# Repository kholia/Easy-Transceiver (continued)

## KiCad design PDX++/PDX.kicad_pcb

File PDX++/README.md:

#### PDX++

A port of https://github.com/WB2CBA/ADX/ to Raspberry Pi Pico.

Bands covered: 80-meter to 10-meter.

The live FT8 audio can also be decoded on PC / RPi / Android phone.

Note: The PCB part is WIP (work-in-progress) at the moment.

####  Features

- Easy inbuilt and self-sufficient Si5351 calibration

- Native FT8 decoding on the Pico (via AA1GD)

- Native spotting (reporting to PSKReporter.info)

- Inbuilt BCI (broadcast interference) filter

#### BOM Sources

International users can buy from Mouser and DigiKey.

Here are some local BOM sources I use:

- https://inkocean.in/ - CD2003 (Chinese clone which is known to work fine)

- https://www.electronicscomp.com/ (SMD resistors + SMD caps + THT inductors)

  - All SMD caps and resistors are 1206 sized

- https://www.ktron.in/ (SMA connectors)

- https://www.comkey.in/ - Branded SMD stuff

- https://rarecomponents.com/store/1002 - NXP 1N4148

- https://projectpoint.in/ - CDIL 7805, PJ307 Stereo Socket

- https://www.evelta.com/l7805-positive-voltage-regulator-1-5a-5v/ (alternate)

- https://robu.in/product/si5351a-i2c-8-khz-160-mhz-clock-generator-breakout-board-module/

- https://robu.in/product/raspberry-pi-pico/

- https://etstore.in/ - OEN MICRO RELAY 46-05-2C

#### Credits

- https://github.com/WB2CBA/ADX/

- https://www.qrz.com/DB/VU2BGS

- https://github.com/aa1gd/pico_ft8_xcvr (AA1GD)

- https://github.com/lu7did/ADX

#### References

- https://github.com/kholia/pico_ft8_xcvr (firmware)

- https://f5npv.wordpress.com/homebrew-ft8qrp-afp-fsk-trx/

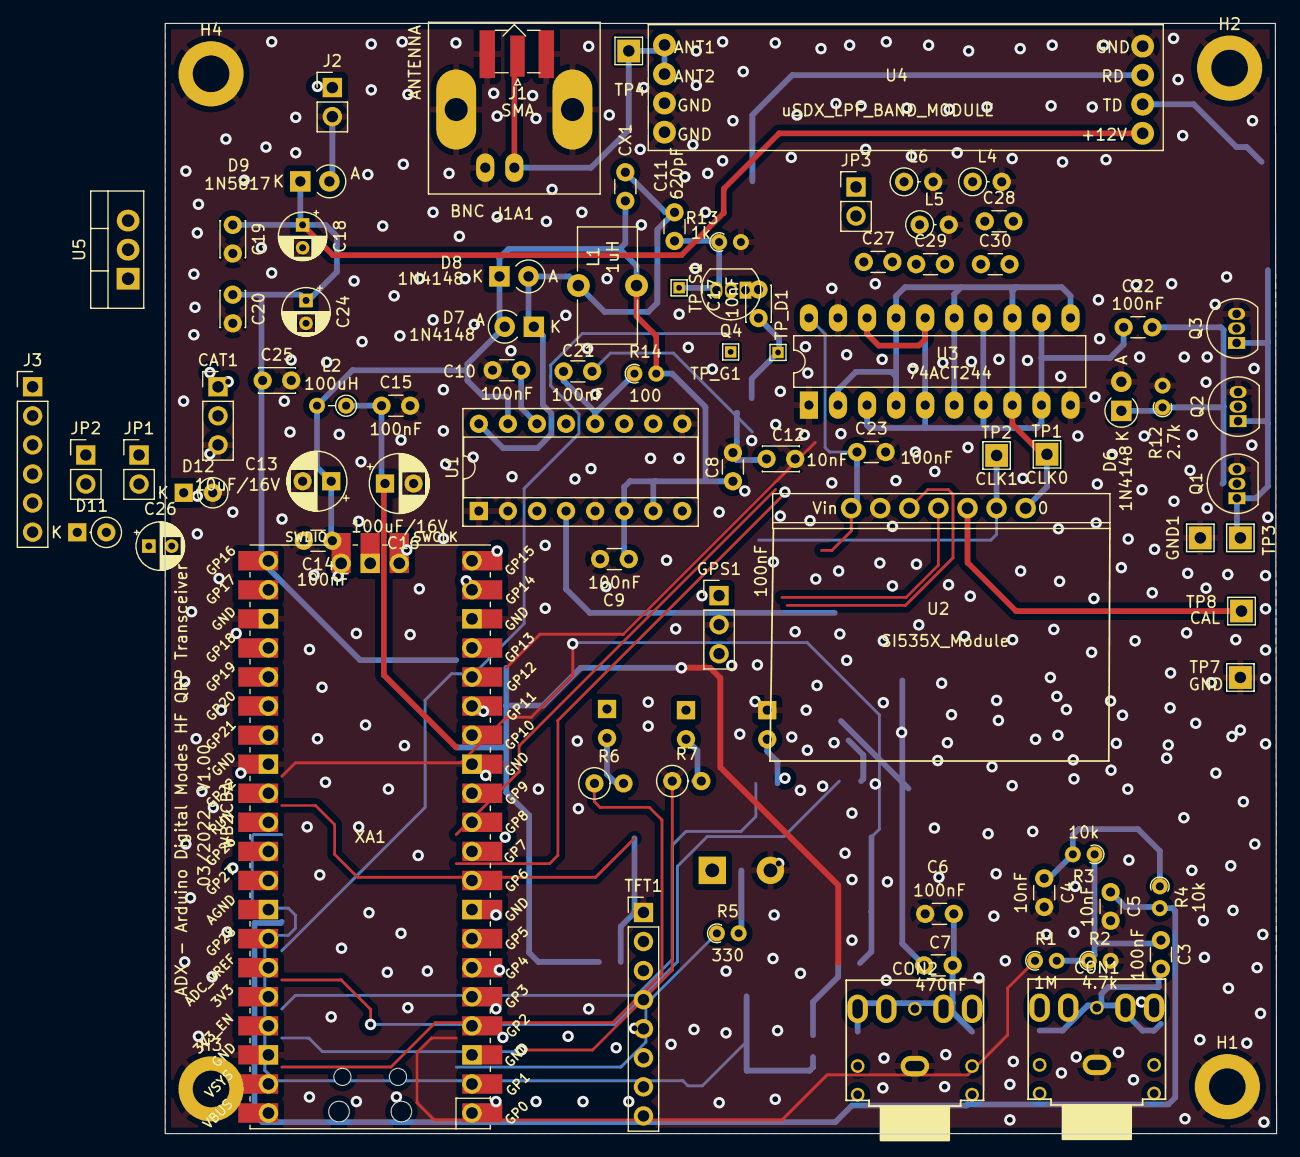
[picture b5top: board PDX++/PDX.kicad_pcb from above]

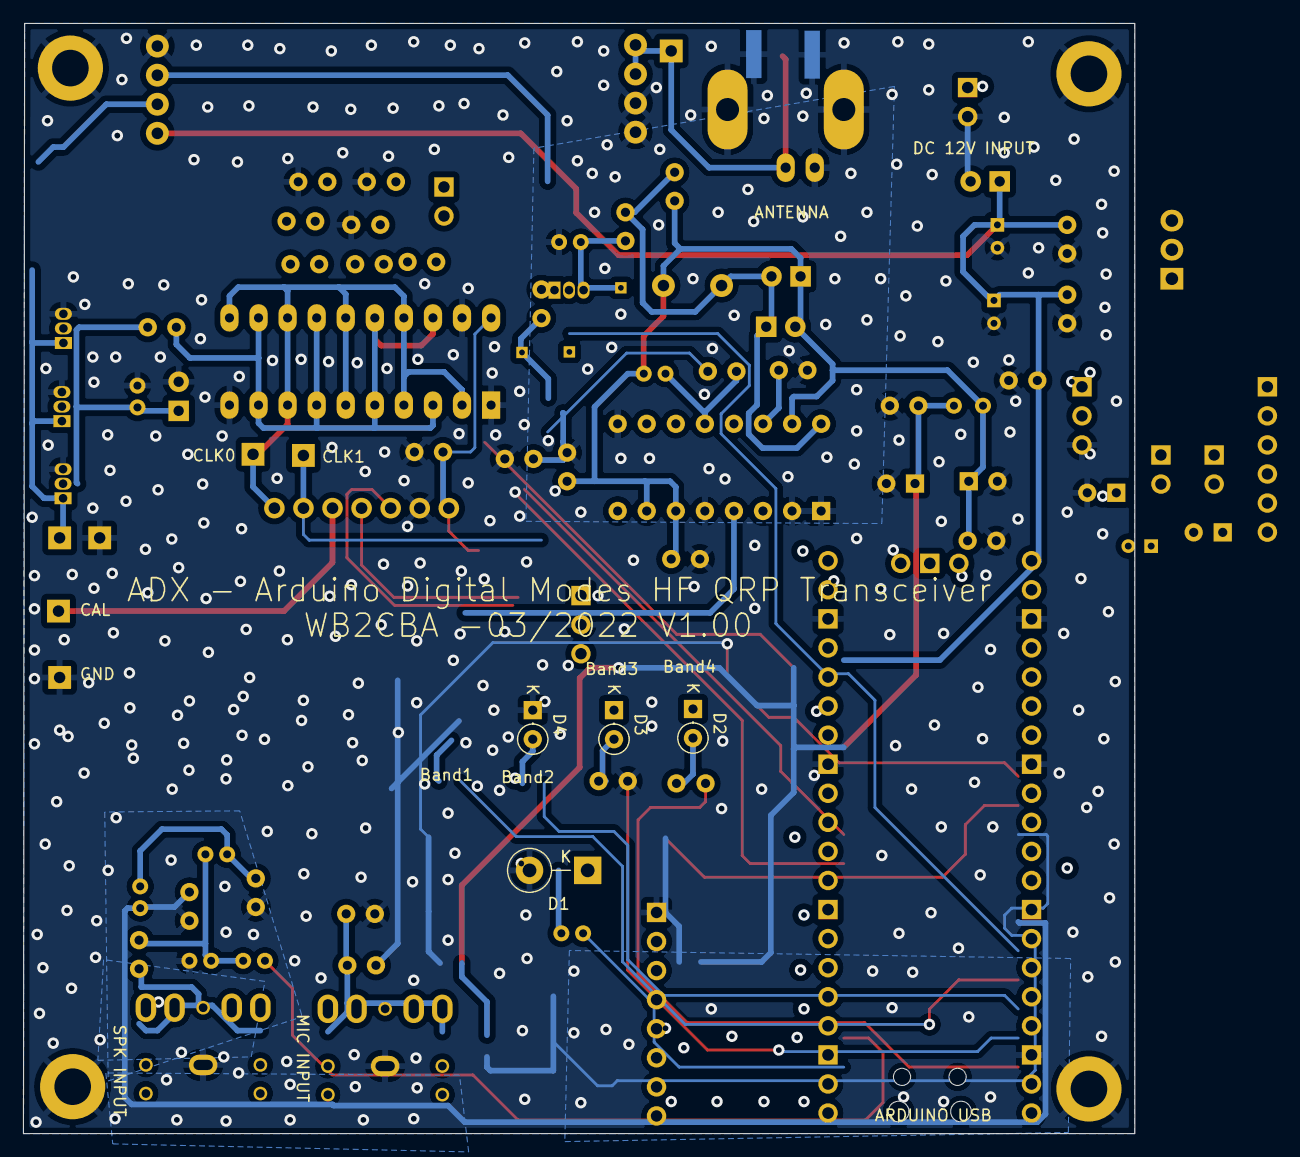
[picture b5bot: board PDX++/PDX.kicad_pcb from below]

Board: 2 copper layers, 97.1 x 97.0 mm, 90 parts (4 on the bottom side), 50 nets.

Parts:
C3, C6, C8, C9, C10, C14, C15, C21, C22, C23: 100nF; C_Disc_D3.0mm_W1.6mm_P2.50mm
C4, C5: 10nF; C_Disc_D3.0mm_W1.6mm_P2.50mm
C7: 470nF; C_Disc_D3.0mm_W1.6mm_P2.50mm
C11: 620pF; C_Disc_D3.0mm_W1.6mm_P2.50mm
C12, C17: 10nF; C_Disc_D3.0mm_W2.0mm_P2.50mm
C13: 10uF/16V; CP_Radial_D5.0mm_P2.50mm
C16: 100uF/16V; CP_Radial_D5.0mm_P2.50mm
C18: 10uF/16V; CP_Radial_D4.0mm_P2.00mm
C19, C20, C25: 100nF; C_Disc_D3.0mm_W2.0mm_P2.50mm
C24: 100uF/16V; CP_Radial_D4.0mm_P2.00mm
C26: 10uF; CP_Radial_D4.0mm_P2.00mm
C27, C30: 2.2nF; C_Disc_D3.0mm_W1.6mm_P2.50mm
C28, C29: 820; C_Disc_D3.0mm_W1.6mm_P2.50mm
CAT1: CAT; PinHeader_1x03_P2.54mm_Vertical
CON1: SPK; PJ-307
CON2: MIC; PJ-307
CX1: C_Disc_D3.0mm_W1.6mm_P2.50mm
D1: 5.6V 5W; D_DO-15_P5.08mm_Vertical_KathodeUp
D2: 1N4001; D_DO-35_SOD27_P2.54mm_Vertical_KathodeUp
D3, D4, D11, D12: 1N4148; D_DO-35_SOD27_P2.54mm_Vertical_KathodeUp
D6: 1N4148; D_A-405_P2.54mm_Vertical_AnodeUp
D7, D8: 1N4148; D_A-405_P2.54mm_Vertical_KathodeUp
D9: 1N5817; D_A-405_P2.54mm_Vertical_KathodeUp
GND1: TestPoint_THTPad_2.0x2.0mm_Drill1.0mm
GPS1: Conn_01x02; PinHeader_1x03_P2.54mm_Vertical
H1, H2, H3, H4: MountingHole_Pad; MountingHole_3.2mm_M3_ISO7380_Pad
J1: SMA; SMA_Samtec_SMA-J-P-X-ST-EM1_EdgeMount
J1A1: BNC; BNC_Amphenol_B6252HB-NPP3G-50_Horizontal
J2: 12v (Max 18v); PinHeader_1x02_P2.54mm_Vertical
J3: IO; PinHeader_1x06_P2.54mm_Vertical
JP1, JP2: Jumper_2_Open; PinHeader_1x02_P2.54mm_Vertical
JP3: Filter-Skip; PinHeader_1x02_P2.54mm_Vertical
L1: 1uH; L_Toroid_Vertical_L10.0mm_W5.0mm_P5.08mm
L2: 100uH; R_Axial_DIN0204_L3.6mm_D1.6mm_P2.54mm_Vertical
L4, L5, L6: 2.2uH; L_Axial_L5.3mm_D2.2mm_P2.54mm_Vertical_Vishay_IM-1
Q1, Q2, Q3, Q4: BS170; TO-92_Inline
R1: 1M; R_Axial_DIN0204_L3.6mm_D1.6mm_P1.90mm_Vertical
R2: 4.7k; R_Axial_DIN0204_L3.6mm_D1.6mm_P1.90mm_Vertical
R3, R4: 10k; R_Axial_DIN0204_L3.6mm_D1.6mm_P1.90mm_Vertical
R5: 330; R_Axial_DIN0204_L3.6mm_D1.6mm_P1.90mm_Vertical
R6, R7: 10k; R_Axial_DIN0207_L6.3mm_D2.5mm_P2.54mm_Vertical
R12: 2.7k; R_Axial_DIN0204_L3.6mm_D1.6mm_P1.90mm_Vertical
R13: 1k; R_Axial_DIN0204_L3.6mm_D1.6mm_P1.90mm_Vertical
R14: 100; R_Axial_DIN0204_L3.6mm_D1.6mm_P1.90mm_Vertical
TFT1: Conn_01x08; PinHeader_1x08_P2.54mm_Vertical
TP1: CLK0; TestPoint_THTPad_2.0x2.0mm_Drill1.0mm
TP2: CLK1; TestPoint_THTPad_2.0x2.0mm_Drill1.0mm
TP3, TP4: TestPoint; TestPoint_THTPad_2.0x2.0mm_Drill1.0mm
TP7: GND; TestPoint_THTPad_2.0x2.0mm_Drill1.0mm
TP8: CAL; TestPoint_THTPad_2.0x2.0mm_Drill1.0mm
TP_D1: TestPoint_THTPad_1.0x1.0mm_Drill0.5mm
TP_G1: TestPoint_THTPad_1.0x1.0mm_Drill0.5mm
TP_S1: TestPoint_THTPad_1.0x1.0mm_Drill0.5mm
U1: CD2003GB_GP; DIP-16_W7.62mm_Socket
U2: SI535X_Module; SI5351 Module_Vertical
U3: 74ACT244; DIP-20_W7.62mm_LongPads
U4: uSDX_LPF_BAND_MODULE; uSDX_LPF_Band_Module
U5: CDIL_7805_TO220; TO-220-3_Vertical
XA1: Pico; RPi_Pico_SMD_TH

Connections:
+3.3V: R1.1, R6.2, TFT1.8, XA1.36 (3V3)
+5V: C15.1, C16.1, C18.1, C19.1, C23.1, C25.1, D1.1 (K), D2.2 (A), J3.4, L2.1, U2.1 (VIN), U3.20 (VCC), U5.3 (VO), XA1.40 (VBUS)
FSK: C5.1, R4.2, XA1.32 (GPIO27_ADC1)
GNDPWR: C4.2, C5.2, C6.2, C8.1, C9.1, C10.1, C12.2, C13.2, C14.2, C15.2, C16.2, C18.2, C19.2, C20.2, C23.2, C24.2, C25.2, CAT1.3, CON1.S, CON2.S, D1.2 (A), D4.1 (K), D6.2 (A), D12.2 (A), GND1.1, GPS1.2, H1.1, H2.1, H3.1, H4.1, J1.2 (Ext), J1A1.2 (Ext), J2.2, J3.5, J3.6, L4.2, L5.2, L6.2, Q1.3 (S), Q2.3 (S), Q3.3 (S), R2.2, R7.1, R12.2, R13.2, TFT1.1, TP7.1, U1.1 (FM_RF_IN), U1.2 (GND_IN), U1.5 (AGC), U1.9 (GND_OUT), U2.2 (GND), U3.1 (OEa), U3.10 (GND), U3.19 (OEb), U4.4 (GND), U4.7 (GND), U4.8 (GND), U5.2 (GND), XA1.13 (GND), XA1.18 (GND), XA1.23 (GND), XA1.28 (GND), XA1.38 (GND)
unnamed: C3.1, R1.2, R2.1, R3.1
unnamed: C3.2, CON1.R, CON1.T
unnamed: C4.1, R3.2, R4.1
unnamed: C6.1, C7.1, CON2.R, CON2.T
unnamed: C10.2, U1.14 (FM/AM_SW)
unnamed: C11.1, Q4.3 (S), R13.1, TP_S1.1
unnamed: C11.2, CX1.1, D7.1 (K), D8.2 (A), L1.1, U1.16 (AM_RF_IN)
unnamed: C8.2, C9.2, C13.1, C14.1, CX1.2, D7.2 (A), D8.1 (K), L1.2, L2.2, R14.2, U1.6 (VCC), U1.7 (AM_IF), U1.15 (FM_TUNER)
unnamed: C17.1, Q4.1 (D), TP_D1.1
unnamed: C17.2, C30.2, JP3.1 (A)
unnamed: C20.1, C24.1, D2.1 (K), D9.1 (K), U4.1 (+12V), U5.1 (VI)
unnamed: C21.1, R14.1, U1.12 (AM_OSC)
unnamed: C22.1, D6.1 (K), Q1.2 (G), Q2.2 (G), Q3.2 (G), R12.1
unnamed: C22.2, U3.3 (O3b), U3.5 (O2b), U3.7 (O1b), U3.9 (O0b), U3.12 (O3a), U3.14 (O2a), U3.16 (O1a), U3.18 (O0a)
unnamed: C26.2, D3.2 (A), D11.1 (K), R5.2
unnamed: C27.2, C28.1, L4.1
unnamed: C28.2, C29.1, L5.1
unnamed: C29.2, C30.1, L6.1
unnamed: CAT1.1, XA1.16 (GPIO12)
unnamed: CAT1.2, XA1.17 (GPIO13)
unnamed: D3.1 (K), D4.2 (A)
unnamed: D9.2 (A), J2.1
unnamed: D11.2 (A), D12.1 (K)
unnamed: J1.1 (In), J1A1.1 (In), TP4.1, U4.5 (ANT1), U4.6 (ANT2)
unnamed: J3.1, XA1.27 (GPIO21)
unnamed: J3.2, XA1.26 (GPIO20)
unnamed: J3.3, XA1.25 (GPIO19)
unnamed: JP1.1 (A), XA1.31 (GPIO26_ADC0)
unnamed: JP2.1 (A), XA1.20 (GPIO15)
unnamed: JP2.2 (B), TP8.1, U2.5 (S2)
unnamed: TFT1.2, XA1.4 (GPIO2)
unnamed: TFT1.3, XA1.5 (GPIO3)
unnamed: TFT1.4, XA1.6 (GPIO4)
unnamed: TFT1.5, XA1.7 (GPIO5)
unnamed: TFT1.6, XA1.9 (GPIO6)
unnamed: TFT1.7, XA1.10 (GPIO7)
unnamed: TP1.1, U2.7 (SO), U3.2 (I0a), U3.4 (I1a), U3.6 (I2a), U3.8 (I3a), U3.11 (I0b), U3.13 (I1b), U3.15 (I2b), U3.17 (I3b)
unnamed: GPS1.1, XA1.11 (GPIO8)
RX: C27.1, JP3.2 (B), U4.3 (RD)
RXA: C7.2, R5.1, U1.4 (AM_MIX)
RXB: C26.1, JP1.2 (B), R6.1, R7.2
RXSW: C12.1, Q4.2 (G), TP_G1.1, XA1.24 (GPIO18)
RX_OSC: C21.2, TP2.1, U2.6 (S1)
SCL: U2.4 (SCL), XA1.22 (GPIO17)
SDA: U2.3 (SDA), XA1.21 (GPIO16)
TD_IN: Q1.1 (D), Q2.1 (D), Q3.1 (D), TP3.1, U4.2 (TD)

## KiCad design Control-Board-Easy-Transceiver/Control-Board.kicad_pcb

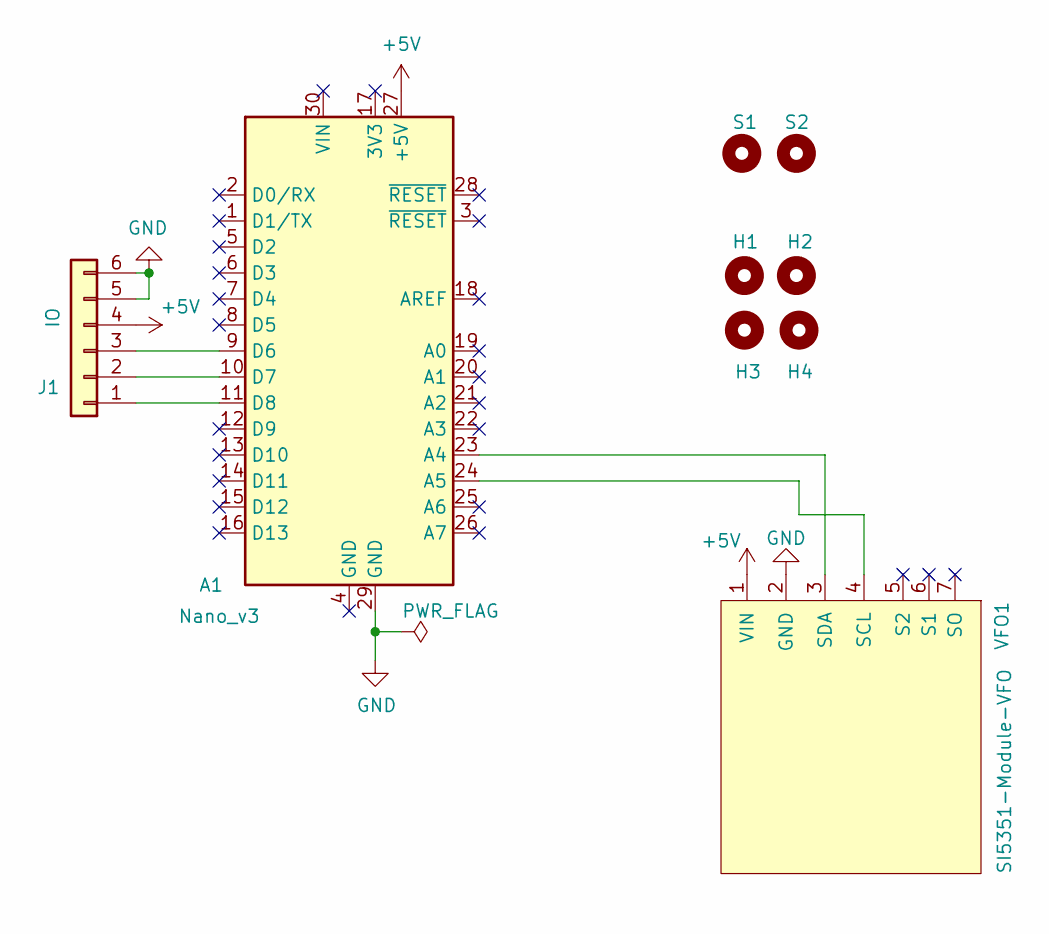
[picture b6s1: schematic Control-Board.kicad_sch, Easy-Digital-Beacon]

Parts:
A1: Nano_v3; Arduino_Nano
H1, H2, H3, H4: MountingHole; MountingHole_2.2mm_M2
J1: IO; PinHeader_1x06_P2.54mm_Vertical
S1, S2: MountingHole; MountingHole_2.7mm_M2.5
VFO1: SI5351-Module-VFO; PinSocket_1x07_P2.54mm_Vertical

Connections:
+5V: A1.27 (+5V), J1.4, VFO1.1 (VIN)
GND: A1.29 (GND), J1.5, J1.6, VFO1.2 (GND)
unnamed: A1.9 (D6), J1.3
unnamed: A1.10 (D7), J1.2
unnamed: A1.11 (D8), J1.1
unnamed: A1.23 (A4), VFO1.3 (SDA)
unnamed: A1.24 (A5), VFO1.4 (SCL)

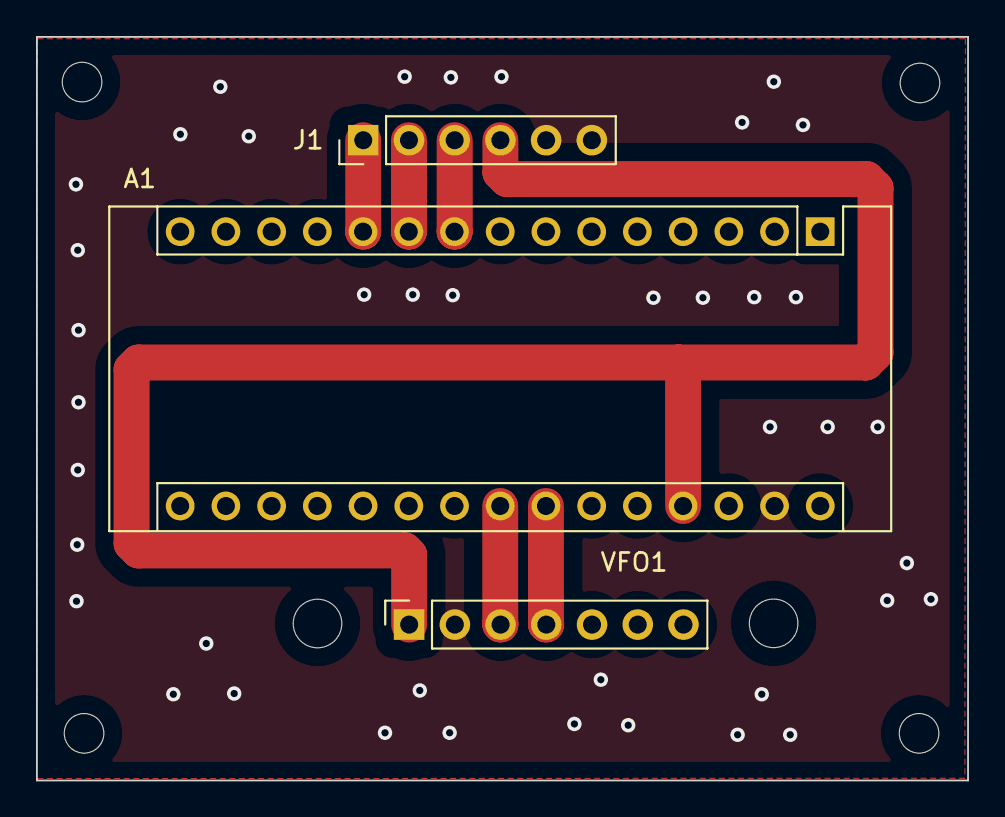
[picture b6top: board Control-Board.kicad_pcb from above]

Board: 2 copper layers, 51.7 x 41.3 mm, 9 parts (0 on the bottom side), 7 nets.
